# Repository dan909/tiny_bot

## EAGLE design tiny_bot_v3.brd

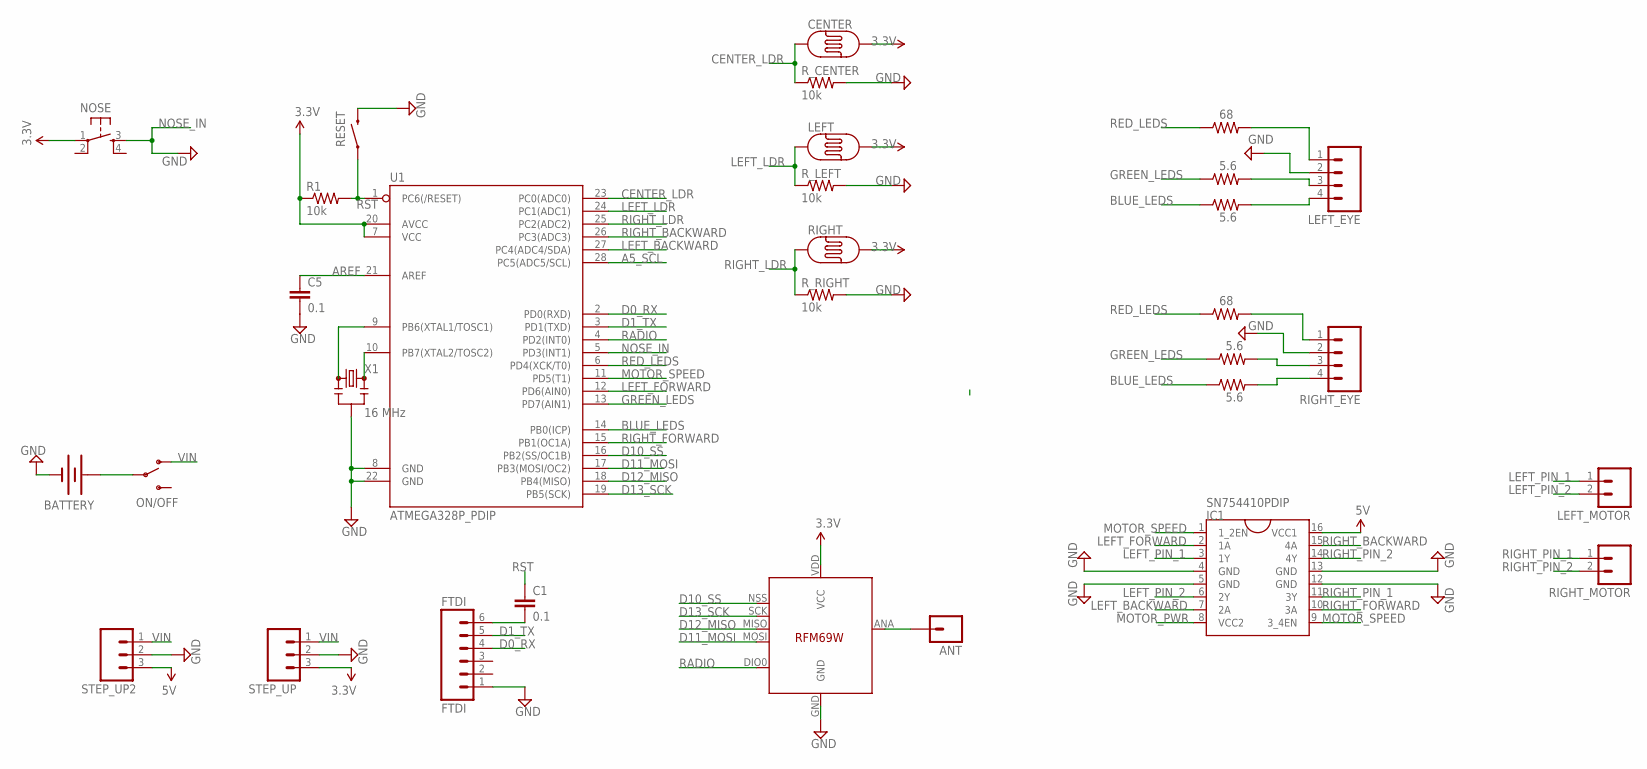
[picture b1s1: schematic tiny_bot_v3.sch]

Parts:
ANT: M01PTH; 1X01
BATTERY: BATTERYAAA; BATTERY-AAA
C1, C5: 0.1; CAP-PTH-SMALL
CENTER: PHOTOCELLPTH; PHOTOCELL
FTDI: FTDI; 1X06
IC1: SN754410PDIP; DIL16
LEFT: PHOTOCELLPTH; PHOTOCELL
LEFT_BLUE: 5.6; AXIAL-0.4
LEFT_EYE: M04LONGPADS; 1X04_LONGPADS
LEFT_GREEN: 5.6; AXIAL-0.4
LEFT_MOTOR: M02PTH; 1X02
LEFT_RED: 68; AXIAL-0.4
NOSE: TACTILE-SWITCH-PTH; TAC-SWITCH-PTH
ON/OFF: SWITCH-SPDTPTH; SWITCH-SPDT
R1: 10k; AXIAL-0.4
RESET: SWITCH-MOMENTARY-2SMD; TACTILE-SWITCH-SMD
RIGHT: PHOTOCELLPTH; PHOTOCELL
RIGHT_BLUE: 5.6; AXIAL-0.4
RIGHT_EYE: M04LONGPADS; 1X04_LONGPADS
RIGHT_GREEN: 5.6; AXIAL-0.4
RIGHT_MOTOR: M02PTH; 1X02
RIGHT_RED: 68; AXIAL-0.4
R_CENTER: 10k; AXIAL-0.4
R_LEFT: 10k; AXIAL-0.4
R_RIGHT: 10k; AXIAL-0.4
STEP_UP, STEP_UP2: M03PTH; 1X03
U1: ATMEGA328P_PDIP; DIL28-3
U$5: RFM69HW; RFM69W-MINPADS
X1: 16 MHz; RESONATOR-PTH

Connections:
5V: IC1.16 (VCC1), STEP_UP2.3
A5_SCL: U1.28 (PC5(ADC5/SCL))
AREF: C5.1, U1.21 (AREF)
BLUE_LEDS: LEFT_BLUE.P$1 (1), RIGHT_BLUE.P$1 (1), U1.14 (PB0(ICP))
CENTER_LDR: CENTER.1, R_CENTER.P$1 (1), U1.23 (PC0(ADC0))
D0_RX: FTDI.4, U1.2 (PD0(RXD))
D1_TX: FTDI.5, U1.3 (PD1(TXD))
D10_SS: U1.16 (PB2(SS/OC1B)), U$5.NSS (SEL)
D11_MOSI: U1.17 (PB3(MOSI/OC2)), U$5.MOSI
D12_MISO: U1.18 (PB4(MISO)), U$5.MISO
D13_SCK: U1.19 (PB5(SCK)), U$5.SCK
GND: BATTERY.GND@1 (-), C5.2, FTDI.1, IC1.4 (GND), IC1.5 (GND), IC1.12 (GND), IC1.13 (GND), LEFT_EYE.2, RESET.3 (2), RIGHT_EYE.2, R_CENTER.P$2 (2), R_LEFT.P$2 (2), R_RIGHT.P$2 (2), STEP_UP.2, STEP_UP2.2, U1.8 (GND), U1.22 (GND), U$5.GND, X1.2
GREEN_LEDS: LEFT_GREEN.P$1 (1), RIGHT_GREEN.P$1 (1), U1.13 (PD7(AIN1))
LEFT_BACKWARD: IC1.7 (2A), U1.27 (PC4(ADC4/SDA))
LEFT_FORWARD: IC1.2 (1A), U1.12 (PD6(AIN0))
LEFT_LDR: LEFT.1, R_LEFT.P$1 (1), U1.24 (PC1(ADC1))
LEFT_PIN_1: IC1.3 (1Y), LEFT_MOTOR.1
LEFT_PIN_2: IC1.6 (2Y), LEFT_MOTOR.2
MOTOR_PWR: IC1.8 (VCC2)
MOTOR_SPEED: IC1.1 (1_2EN), IC1.9 (3_4EN), U1.11 (PD5(T1))
unnamed: U1.9 (PB6(XTAL1/TOSC1)), X1.1
unnamed: ANT.1, U$5.ANA (ANT)
unnamed: LEFT_EYE.1, LEFT_RED.P$2 (2)
unnamed: RIGHT_EYE.1, RIGHT_RED.P$2 (2)
unnamed: LEFT_EYE.3, LEFT_GREEN.P$2 (2)
unnamed: LEFT_BLUE.P$2 (2), LEFT_EYE.4
unnamed: RIGHT_EYE.3, RIGHT_GREEN.P$2 (2)
unnamed: RIGHT_BLUE.P$2 (2), RIGHT_EYE.4
unnamed: BATTERY.PWR@1 (+), ON/OFF.2
unnamed: C1.2, FTDI.6
unnamed: U1.10 (PB7(XTAL2/TOSC2)), X1.3
NOSE_IN: NOSE.3, U1.5 (PD3(INT1))
RADIO: U1.4 (PD2(INT0)), U$5.DIO0
RED_LEDS: LEFT_RED.P$1 (1), RIGHT_RED.P$1 (1), U1.6 (PD4(XCK/T0))
RIGHT_BACKWARD: IC1.15 (4A), U1.26 (PC3(ADC3))
RIGHT_FORWARD: IC1.10 (3A), U1.15 (PB1(OC1A))
RIGHT_LDR: RIGHT.1, R_RIGHT.P$1 (1), U1.25 (PC2(ADC2))
RIGHT_PIN_1: IC1.11 (3Y), RIGHT_MOTOR.1
RIGHT_PIN_2: IC1.14 (4Y), RIGHT_MOTOR.2
RST: C1.1, R1.P$2 (2), RESET.1, U1.1 (PC6(/RESET))
VCC: CENTER.2, LEFT.2, NOSE.1, R1.P$1 (1), RIGHT.2, STEP_UP.3, U1.7 (VCC), U1.20 (AVCC), U$5.VDD (VCC)
VIN: ON/OFF.1 (O), STEP_UP.1, STEP_UP2.1

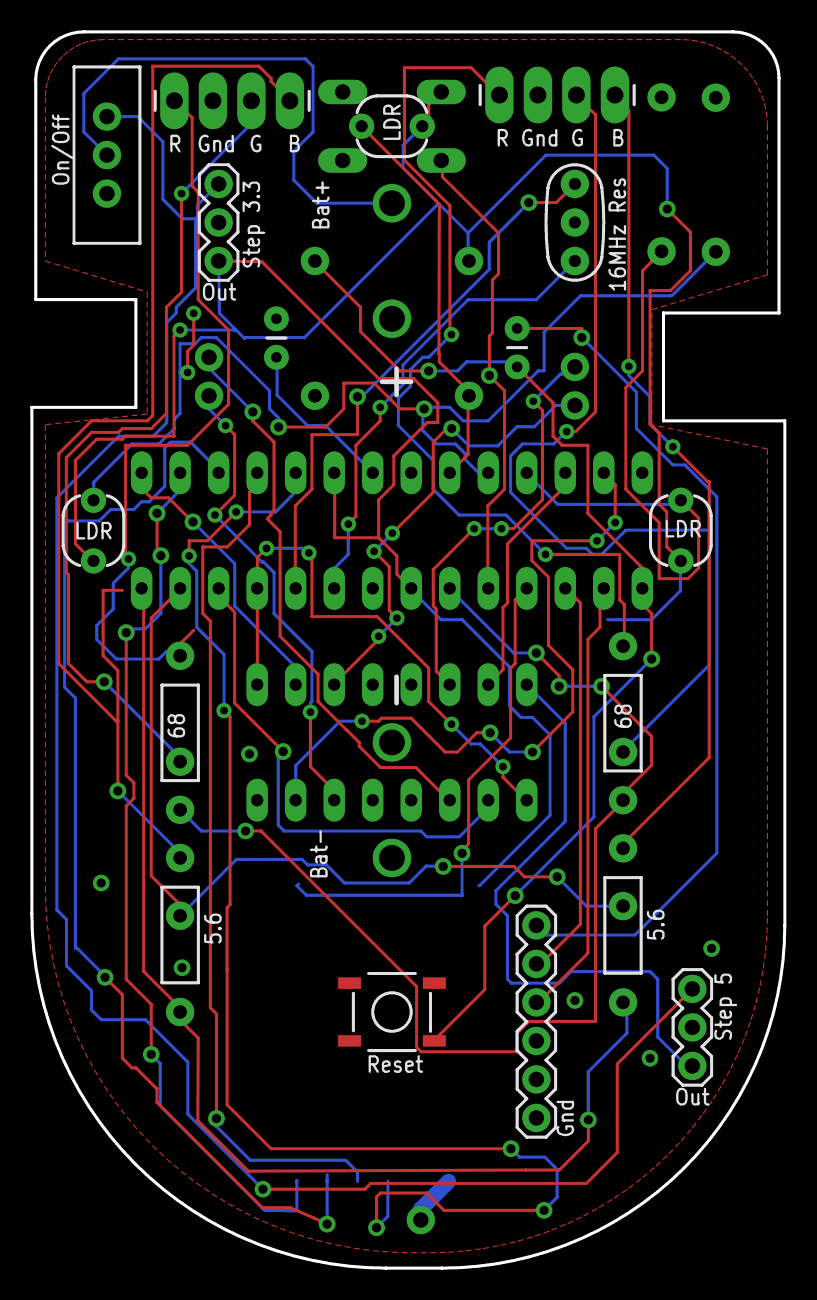
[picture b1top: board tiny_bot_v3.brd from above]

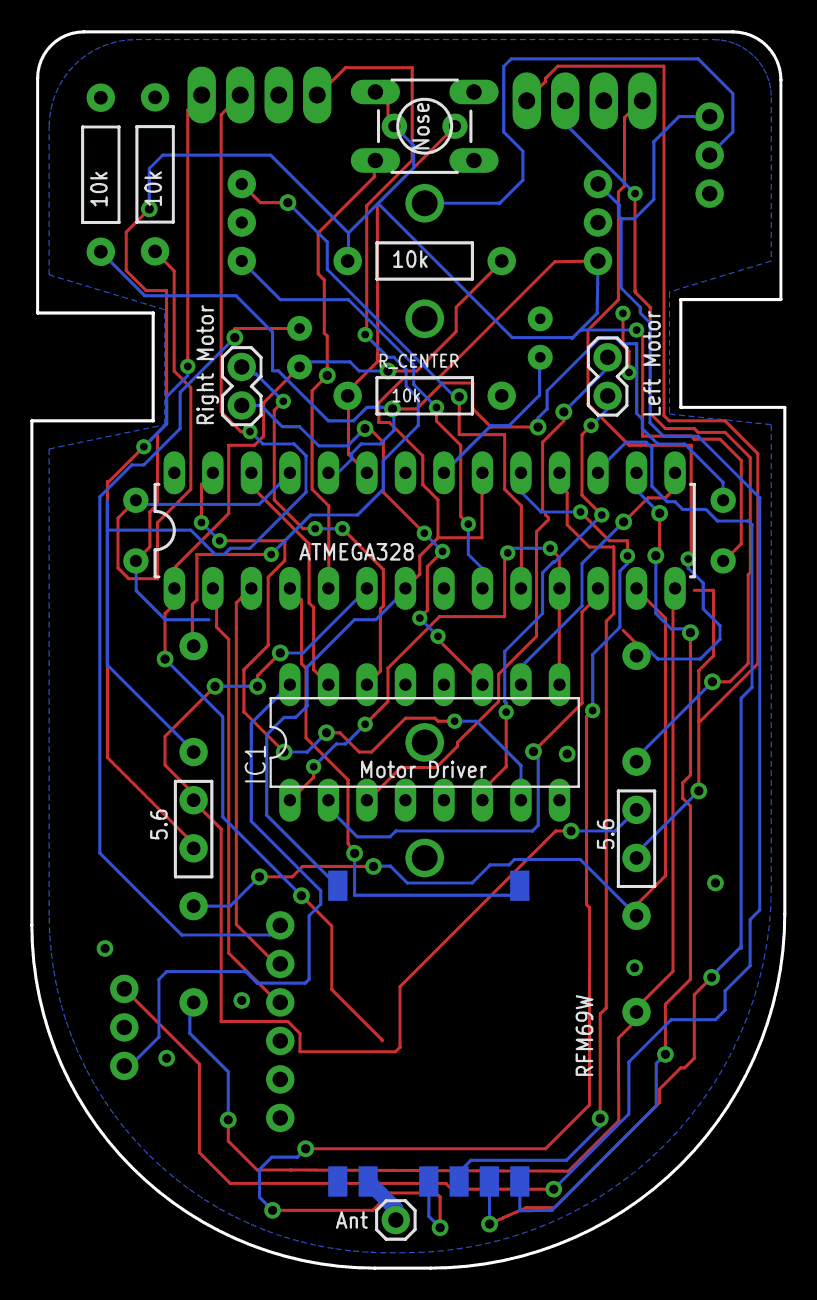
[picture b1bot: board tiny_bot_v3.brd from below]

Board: 2 copper layers, 49.7 x 81.5 mm, 31 parts (13 on the bottom side), 40 nets.

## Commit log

2016-10-01 Initial commit of schematic file
2016-10-01 Finished schematic and added board file
2016-10-02 Fixed LED problem; Started board layout
2016-10-28 Finished routing (probably)
2016-10-29 Adding gerbers
2017-01-10 Adding gerber files
2017-01-10 Adding images of PCB
2017-07-16 V3 has an on/off switch and seperate step-up regulator for the motor driver
2017-07-16 Fixed clearance error and added gerber files

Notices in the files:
parts and their libraries:
SparkFun-FreqCtrl: Licensing: Creative Commons ShareAlike 4.0 International - https://creativecommons.org/licenses/by-sa/4.0
SparkFun-Connectors: Licensing: CC v3.0 Share-Alike You are welcome to use this library for commercial purposes.
